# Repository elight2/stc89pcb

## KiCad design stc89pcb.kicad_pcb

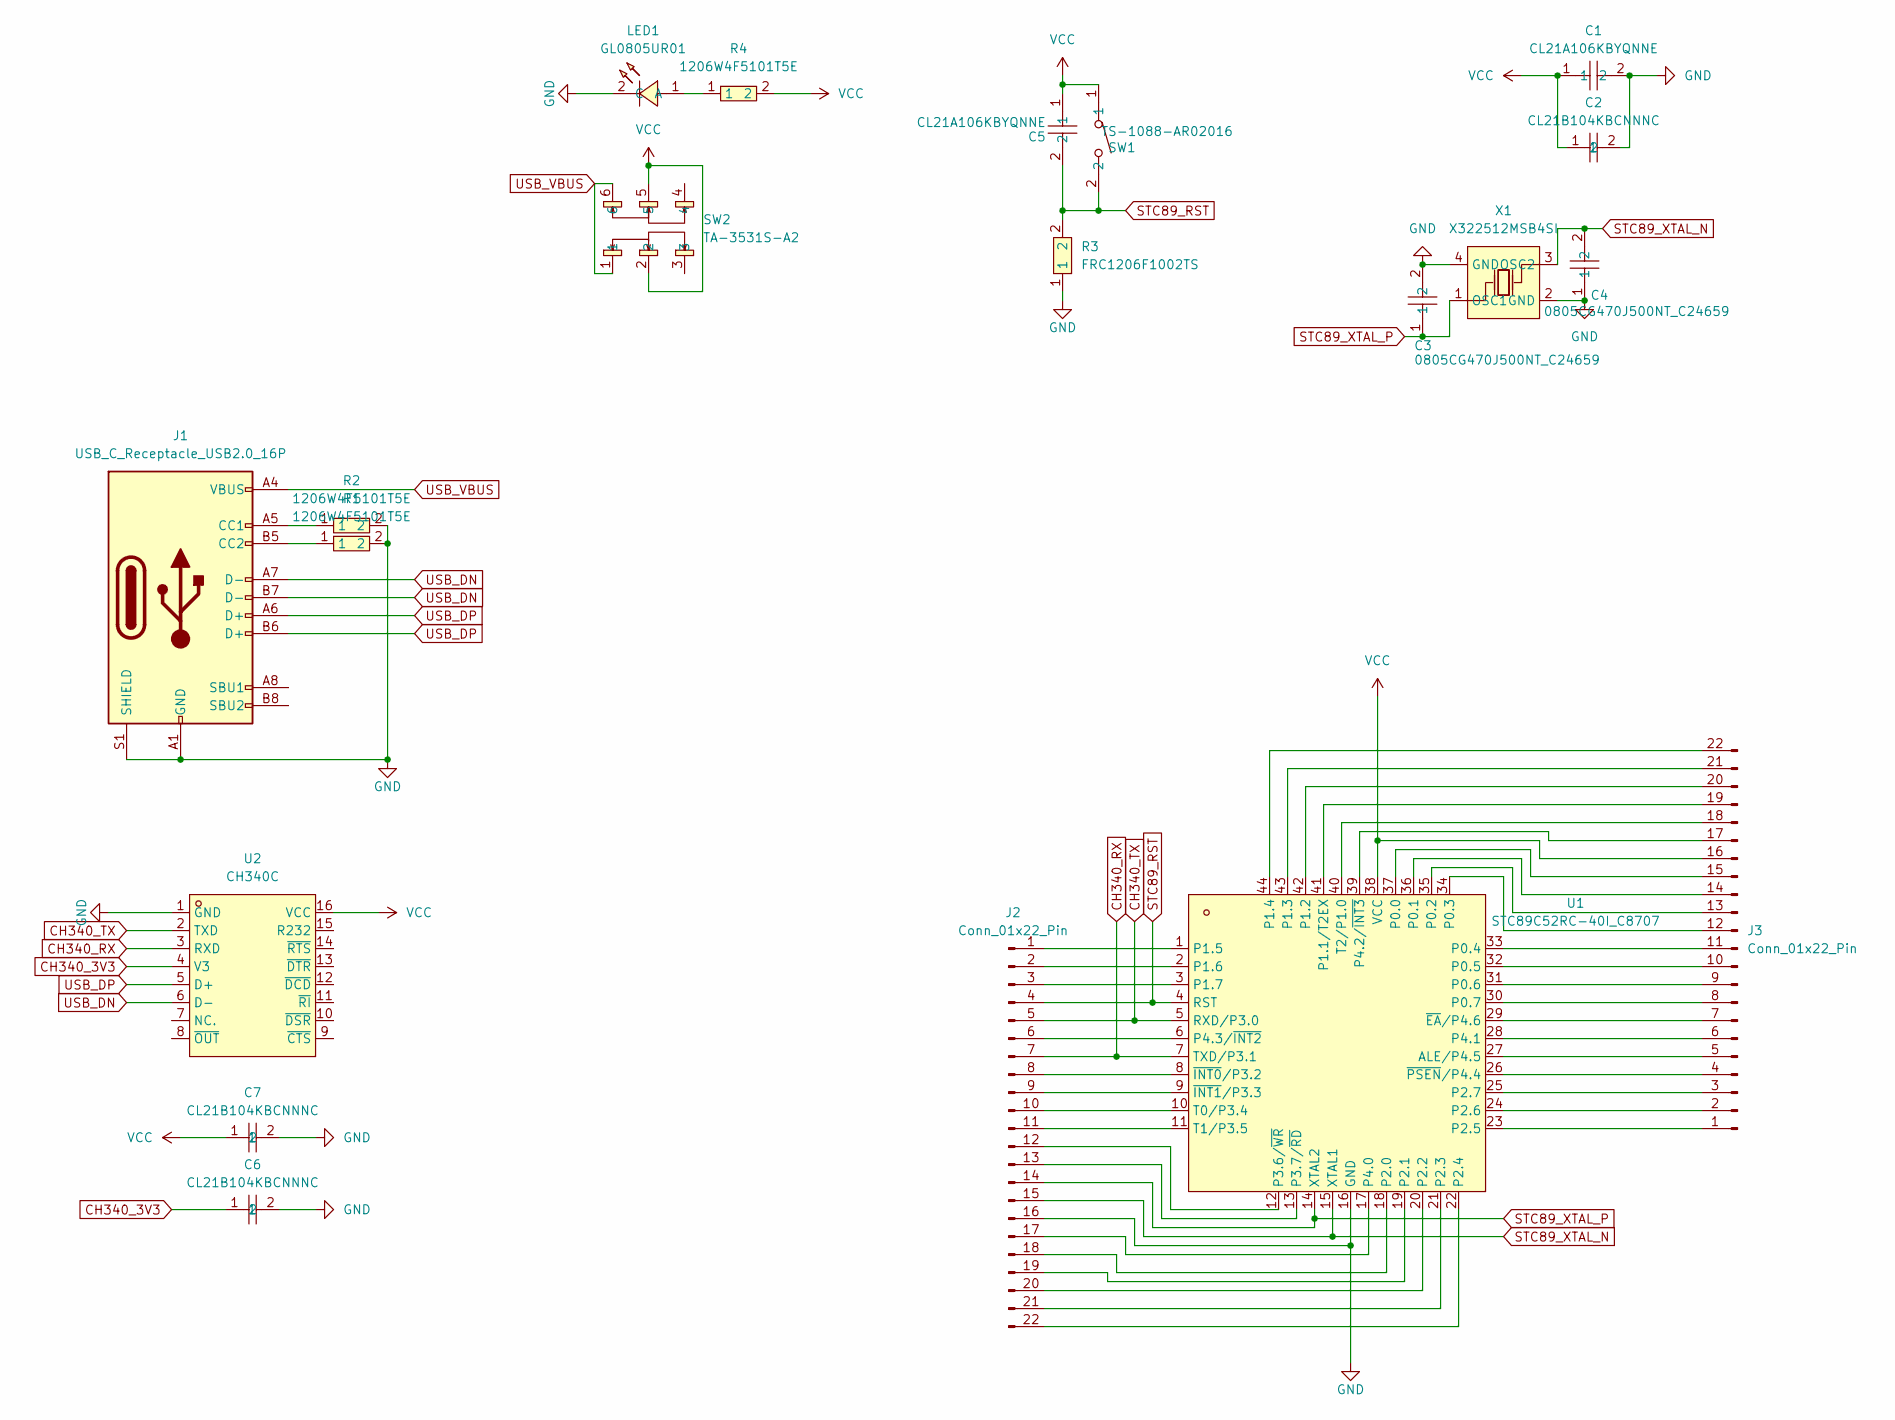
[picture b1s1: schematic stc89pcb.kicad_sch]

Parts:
C1, C5: CL21A106KBYQNNE; C0805; LCSC Part C2932476
C2, C6, C7: CL21B104KBCNNNC; C0805; LCSC Part C1711
C3, C4: 0805CG470J500NT_C24659; C0805; LCSC Part C24659
J1: USB_C_Receptacle_USB2.0_16P; USB_C_Receptacle_GCT_USB4105-xx-A_16P_TopMnt_Horizontal
J2, J3: Conn_01x22_Pin; PinHeader_1x22_P2.54mm_Vertical
LED1: GL0805UR01; LED0805-R-RD_RED; LCSC Part C51933307
R1, R2, R4: 1206W4F5101T5E; R1206; LCSC Part C26033
R3: FRC1206F1002TS; R1206; LCSC Part C2907370
SW1: TS-1088-AR02016; SW-SMD_L3.9-W3.0-P4.45; LCSC Part C720477
SW2: TA-3531S-A2; SW-SMD_6P-L9.1-W3.5-P2.50; LCSC Part C514034
U1: STC89C52RC-40I_C8707; LQFP-44_L10.0-W10.0-P0.80-LS12.0-BL; LCSC Part C8707
U2: CH340C; SOP-16_L10.0-W3.9-P1.27-LS6.0-BL; LCSC Part C84681
X1: X322512MSB4SI; CRYSTAL-SMD_4P-L3.2-W2.5-BL; LCSC Part C9002

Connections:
CH340_3V3: C6.1, U2.4 (V3)
CH340_RX: J2.7, U1.7 (TXD/P3.1), U2.3 (RXD)
CH340_TX: J2.5, U1.5 (RXD/P3.0), U2.2 (TXD)
GND: C1.2, C2.2, C3.2, C4.1, C6.2, C7.2, J1.A1 (GND), J1.A12 (GND), J1.B1 (GND), J1.B12 (GND), J1.S1 (SHIELD), J2.16, LED1.2 (C), R1.2, R2.2, R3.1, U1.16 (GND), U2.1 (GND), X1.2 (GND), X1.4 (GND)
unnamed: J1.A5 (CC1), R2.1
unnamed: J1.B5 (CC2), R1.1
unnamed: J2.1, U1.1 (P1.5)
unnamed: J2.2, U1.2 (P1.6)
unnamed: J2.3, U1.3 (P1.7)
unnamed: J2.6, U1.6 (P4.3/~INT2)
unnamed: J2.8, U1.8 (~INT0/P3.2)
unnamed: J2.9, U1.9 (~INT1/P3.3)
unnamed: J2.10, U1.10 (T0/P3.4)
unnamed: J2.11, U1.11 (T1/P3.5)
unnamed: J2.12, U1.12 (P3.6/~WR)
unnamed: J2.13, U1.13 (P3.7/~RD)
unnamed: J2.17, U1.17 (P4.0)
unnamed: J2.18, U1.18 (P2.0)
unnamed: J2.19, U1.19 (P2.1)
unnamed: J2.20, U1.20 (P2.2)
unnamed: J2.21, U1.21 (P2.3)
unnamed: J2.22, U1.22 (P2.4)
unnamed: J3.1, U1.23 (P2.5)
unnamed: J3.2, U1.24 (P2.6)
unnamed: J3.3, U1.25 (P2.7)
unnamed: J3.4, U1.26 (~PSEN/P4.4)
unnamed: J3.5, U1.27 (ALE/P4.5)
unnamed: J3.6, U1.28 (P4.1)
unnamed: J3.7, U1.29 (~EA/P4.6)
unnamed: J3.8, U1.30 (P0.7)
unnamed: J3.9, U1.31 (P0.6)
unnamed: J3.10, U1.32 (P0.5)
unnamed: J3.11, U1.33 (P0.4)
unnamed: J3.12, U1.34 (P0.3)
unnamed: J3.13, U1.35 (P0.2)
unnamed: J3.14, U1.36 (P0.1)
unnamed: J3.15, U1.37 (P0.0)
unnamed: J3.17, U1.39 (P4.2/~INT3)
unnamed: J3.18, U1.40 (T2/P1.0)
unnamed: J3.19, U1.41 (P1.1/T2EX)
unnamed: J3.20, U1.42 (P1.2)
unnamed: J3.21, U1.43 (P1.3)
unnamed: J3.22, U1.44 (P1.4)
unnamed: LED1.1 (A), R4.1
STC89_RST: C5.2, J2.4, R3.2, SW1.2, U1.4 (RST)
STC89_XTAL_N: C4.2, J2.15, U1.15 (XTAL1), X1.3 (OSC2)
STC89_XTAL_P: C3.1, J2.14, U1.14 (XTAL2), X1.1 (OSC1)
USB_DN: J1.A7 (D-), J1.B7 (D-), U2.6 (D-)
USB_DP: J1.A6 (D+), J1.B6 (D+), U2.5 (D+)
USB_VBUS: J1.A4 (VBUS), J1.A9 (VBUS), J1.B4 (VBUS), J1.B9 (VBUS), SW2.1, SW2.6
VCC: C1.1, C2.1, C5.1, C7.1, J3.16, R4.2, SW1.1, SW2.2, SW2.5, U1.38 (VCC), U2.16 (VCC)

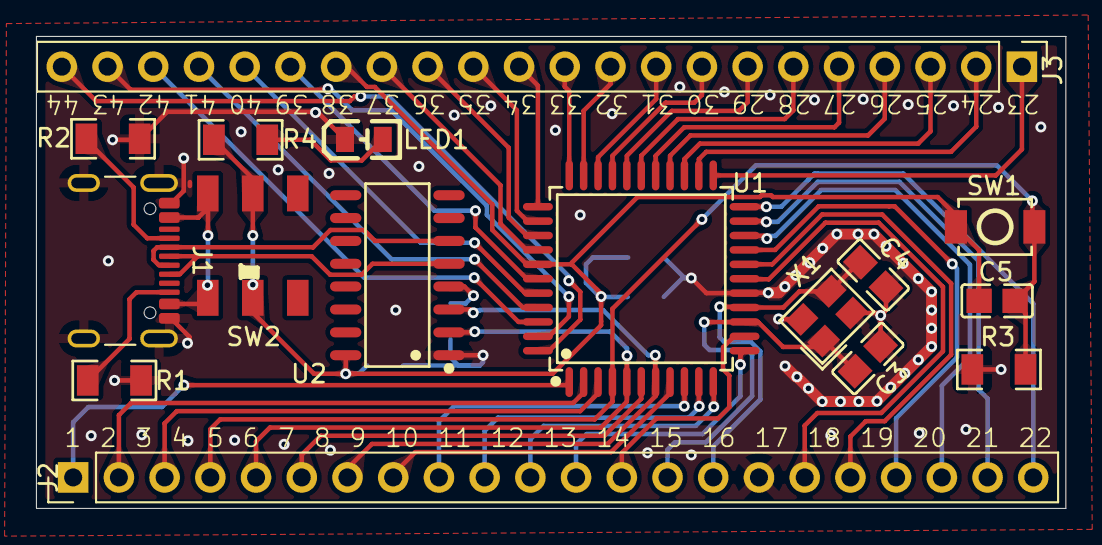
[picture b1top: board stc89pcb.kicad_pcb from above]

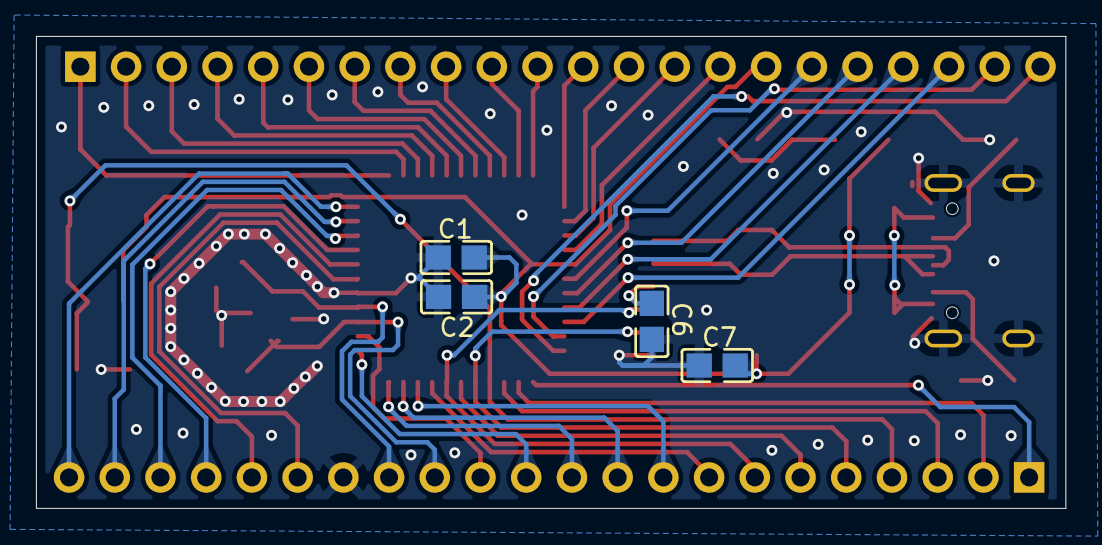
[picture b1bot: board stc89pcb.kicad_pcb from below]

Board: 2 copper layers, 57.2 x 26.2 mm, 20 parts (4 on the bottom side), 51 nets.

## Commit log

2026-03-02 first
